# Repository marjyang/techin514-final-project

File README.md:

# Smart Shower Feedback System

This device focuses on the issue of water usage waste and awareness during long showers - an important issue for utility bills and sustainability.

This system will monitor real-time water usage directly from the shower head (sensing device) and provide feedback to users with a meter and OLED on the other side of the shower wall (display device) to remind users of their water consumption habits. Users will also be able to set weekly water consumption goals.

## The "sensor" device

The sensing device, YF-S201, is connected to the ESP32 from the sensing device, and measures the flow rate of water directly from the showerhead. It generates pulse signals proportional to the water usage, where the ESP32 can process as metrics like total water consumed and flow rate. 

## The "display" device

The display device has an OLED screen, gauge needle and LEDs controlled by its own ESP32 microcontroller. From the water usage data from the sensing device ESP32, the ESP32 here helps display real-time feedback including water consumed during the week and processes data to track progress toward weekly consumption goal. The buttons connected also allow users to manually adjust the gauge needle or the weekly goal set.

## System Architecture
### Diagram 1

### Diagram 2

Here, the YF-S201 sensor sends data from the shower through GPIO connection with the sensing device XIAO ESP32, where the data is processed. This ESP32 then through, HTTP request, sends the processed data to the display device ESP32 wirelessly. This ESP32 through GPIO controls the output in the LEDs and another GPIO controlling output in the gauge needle. Through I2C/SPI, the ESP32 displays the processed data onto the SSD1306 OLED display. Buttons are also connected to the GPIO of the ESP32, where input data from interacting with buttons is sent over as data to the gauge needle to control the weekly goal set.

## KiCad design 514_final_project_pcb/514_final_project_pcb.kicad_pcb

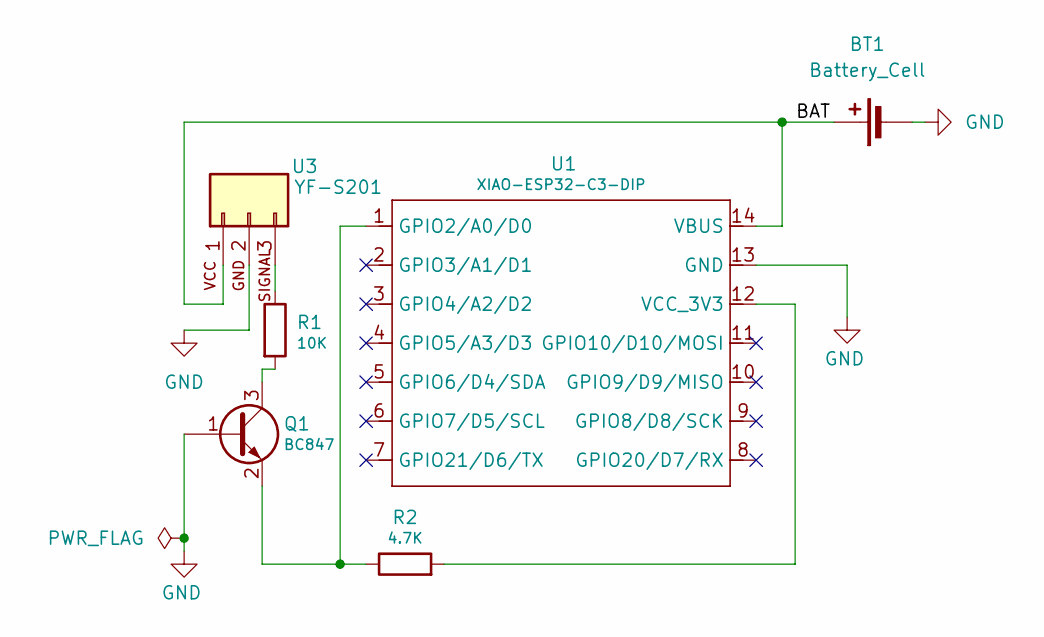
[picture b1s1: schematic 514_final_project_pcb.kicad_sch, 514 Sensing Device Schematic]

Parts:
BT1: Battery_Cell; JST_NV_B02P-NV_1x02_P5.00mm_Vertical
Q1: BC847; SOT-23
R1: 10K; R_0805_2012Metric
R2: 4.7K; R_0805_2012Metric
U1: XIAO-ESP32-C3-DIP; XIAO-ESP32C3-DIP
U3: YF-S201; PinSocket_1x03_P2.54mm_Vertical

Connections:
/BAT: BT1.1 (+), U1.14 (VBUS), U3.1 (VCC)
GND: BT1.2 (-), Q1.1 (B), U1.13 (GND), U3.2 (GND)
unnamed: Q1.3 (C), R1.2
unnamed: Q1.2 (E), R2.1, U1.1 (GPIO2/A0/D0)
unnamed: R2.2, U1.12 (VCC_3V3)
unnamed: R1.1, U3.3 (SIGNAL)

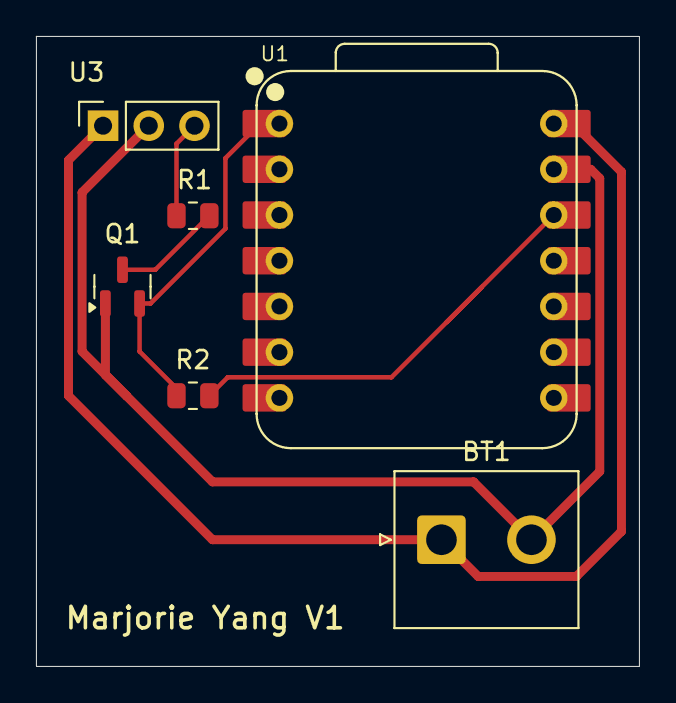
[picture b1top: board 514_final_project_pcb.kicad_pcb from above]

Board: 2 copper layers, 33.5 x 35.0 mm, 6 parts (0 on the bottom side), 6 nets.

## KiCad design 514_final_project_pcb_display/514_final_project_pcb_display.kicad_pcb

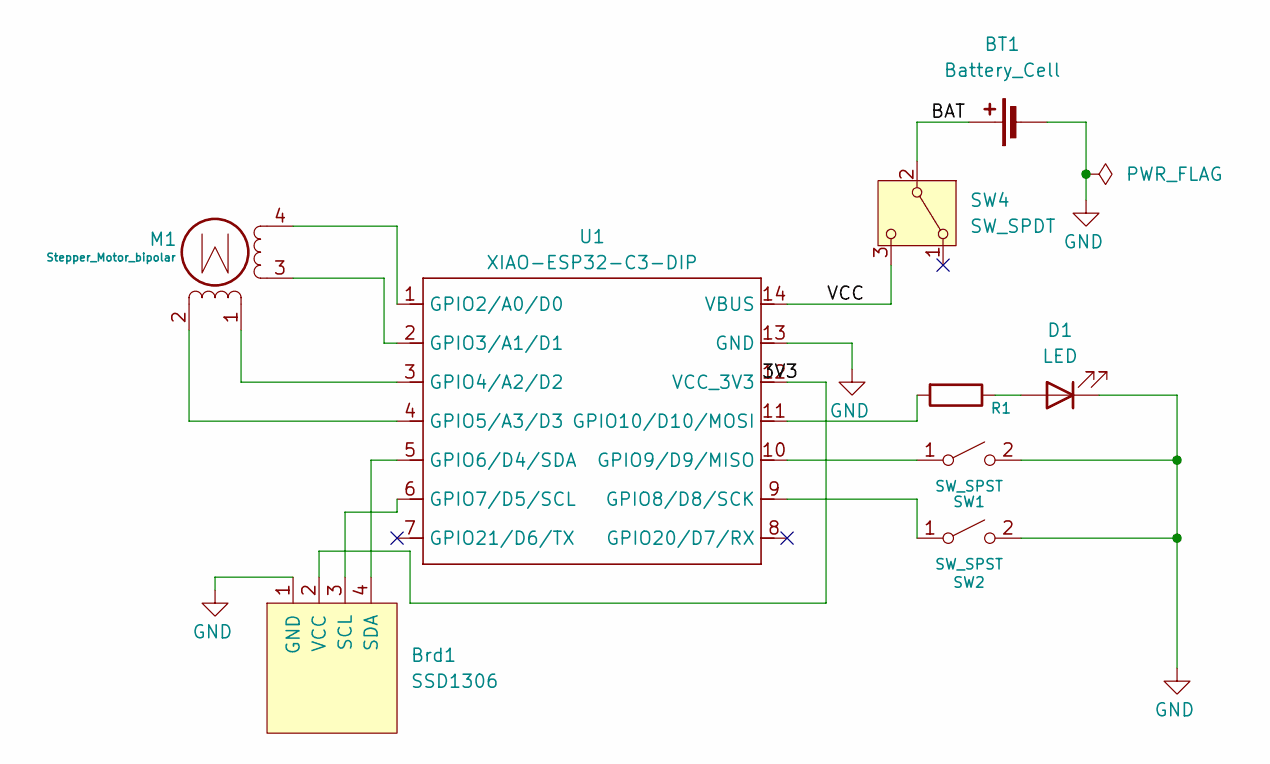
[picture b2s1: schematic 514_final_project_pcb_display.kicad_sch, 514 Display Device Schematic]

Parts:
BT1: Battery_Cell; JST_NV_B02P-NV_1x02_P5.00mm_Vertical
Brd1: SSD1306; 128x64OLED
D1: LED; LED_1206_3216Metric
M1: Stepper_Motor_bipolar; x27_stepper
R1: 220; R_0603_1608Metric
SW1, SW2: SW_SPST; SW_PUSH-12mm
SW4: SW_SPDT; JST_EH_B3B-EH-A_1x03_P2.50mm_Vertical
U1: XIAO-ESP32-C3-DIP; XIAO-ESP32C3-DIP

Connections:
/BAT: BT1.1 (+), SW4.2 (B)
/VCC: SW4.3 (C), U1.14 (VBUS)
GND: BT1.2 (-), Brd1.1 (GND), D1.1 (K), SW1.2 (B), SW2.2 (B), U1.13 (GND)
unnamed: Brd1.3 (SCL), U1.6 (GPIO7/D5/SCL)
unnamed: Brd1.4 (SDA), U1.5 (GPIO6/D4/SDA)
unnamed: Brd1.2 (VCC), U1.12 (VCC_3V3)
unnamed: D1.2 (A), R1.1
unnamed: M1.2 (-), U1.4 (GPIO5/A3/D3)
unnamed: SW1.1 (A), U1.10 (GPIO9/D9/MISO)
unnamed: SW2.1 (A), U1.9 (GPIO8/D8/SCK)
unnamed: M1.4, U1.1 (GPIO2/A0/D0)
unnamed: M1.3, U1.2 (GPIO3/A1/D1)
unnamed: M1.1, U1.3 (GPIO4/A2/D2)
unnamed: R1.2, U1.11 (GPIO10/D10/MOSI)

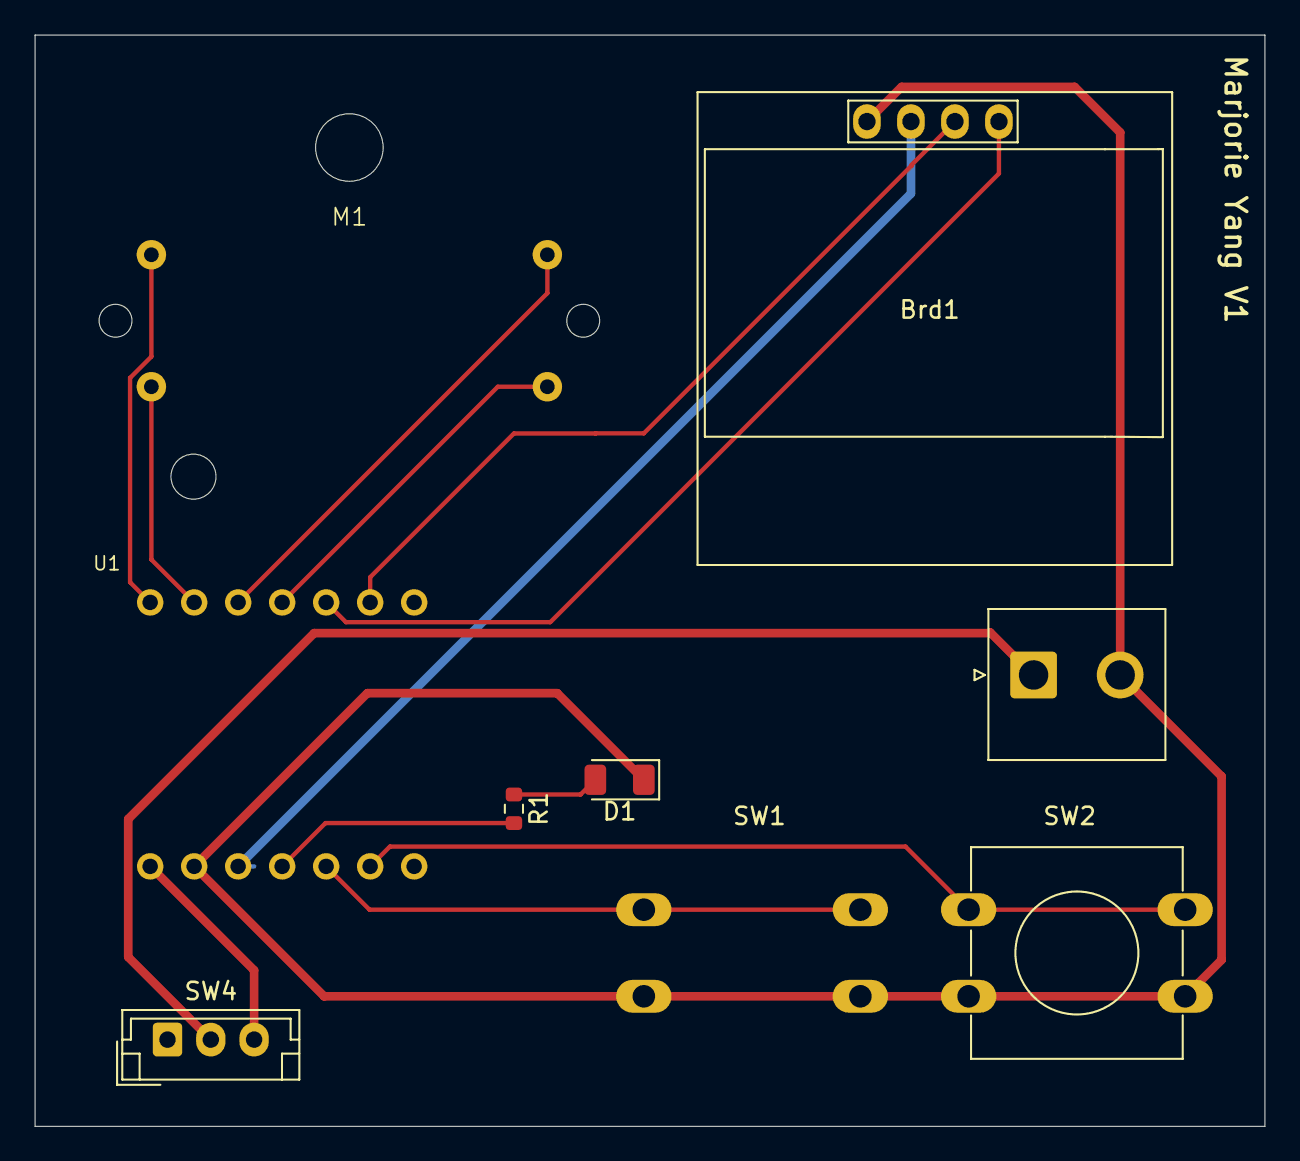
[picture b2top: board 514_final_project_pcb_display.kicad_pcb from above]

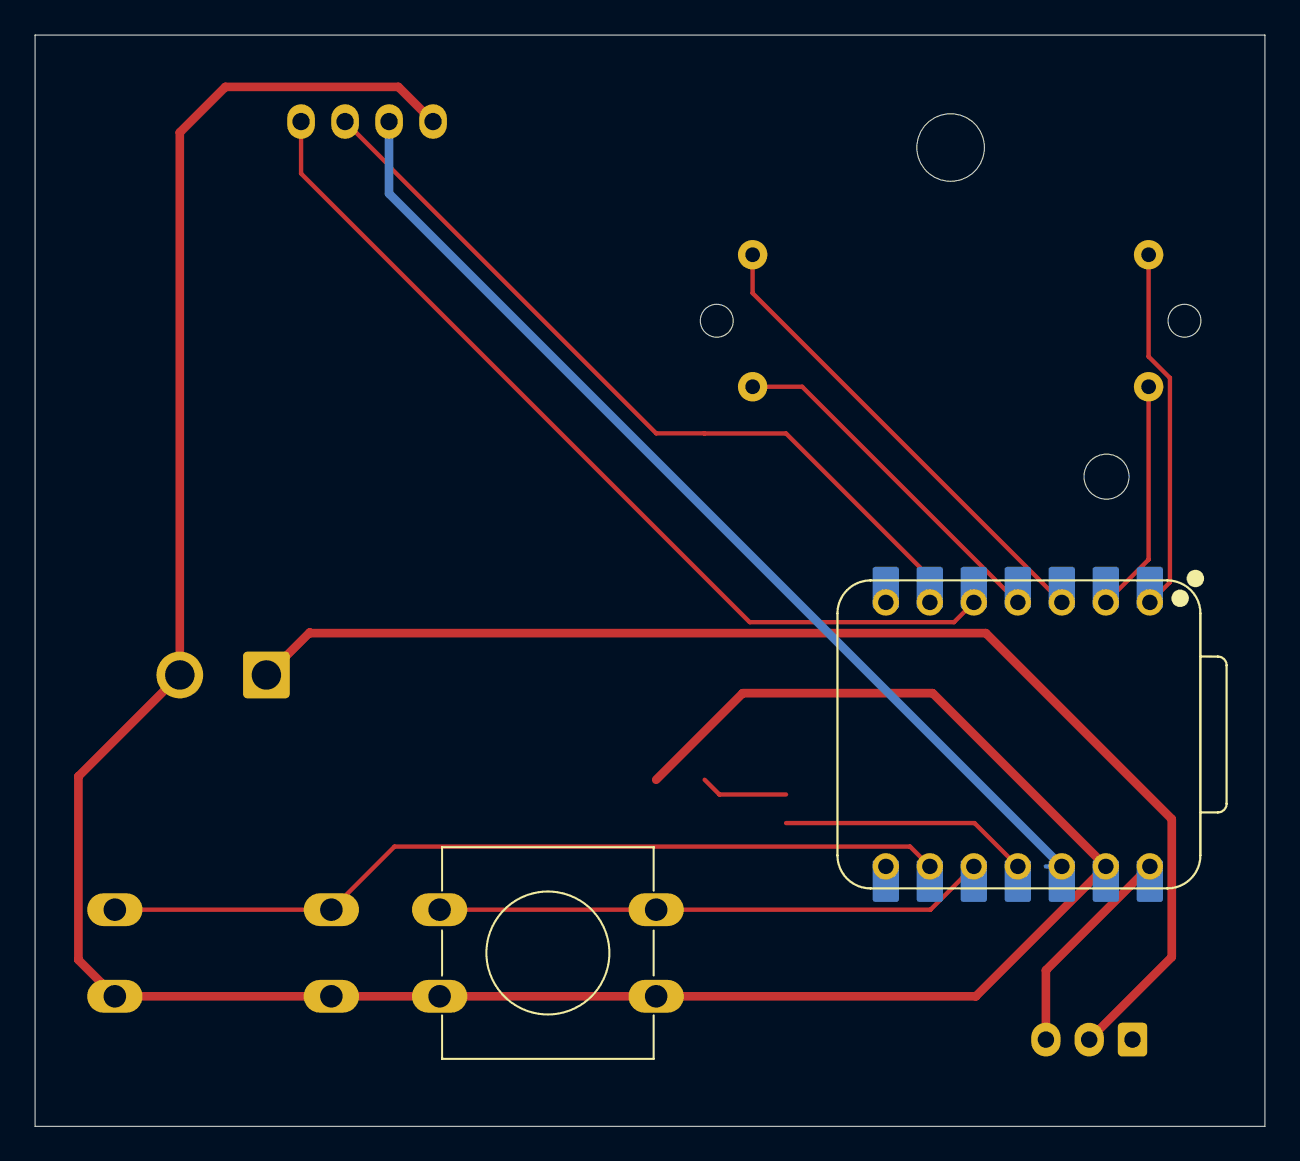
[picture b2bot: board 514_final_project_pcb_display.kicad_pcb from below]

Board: 2 copper layers, 71.0 x 63.0 mm, 9 parts (2 on the bottom side), 14 nets.

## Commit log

2025-01-22 Added datasheets
2025-01-27 added pcb schematic kicad
2025-02-13 updated files
2025-03-11 deleted files
2025-03-11 Remove
2025-03-11 add back
